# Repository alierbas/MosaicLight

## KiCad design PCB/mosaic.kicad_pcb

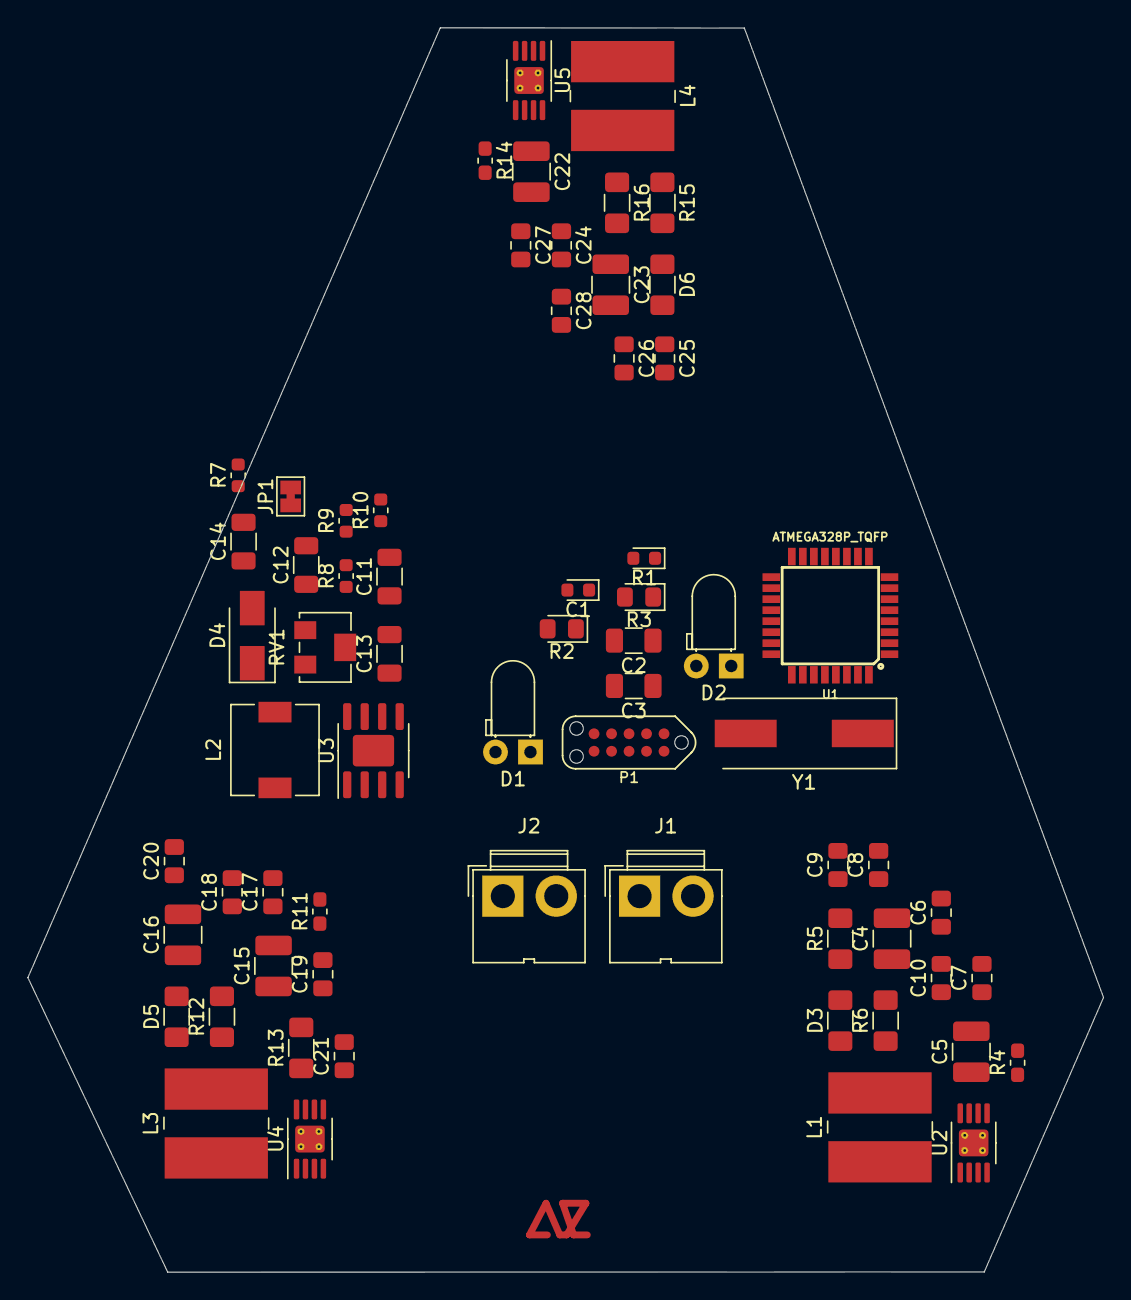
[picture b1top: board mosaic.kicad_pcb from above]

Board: 2 copper layers, 78.1 x 90.3 mm, 66 parts (0 on the bottom side), 33 nets, no tracks yet.

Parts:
C1: 0.1u; LED_0603_1608Metric
C2, C3: C; C_1206_3216Metric
C4, C5, C15, C16, C22, C23: 4.7 uF; C_1210_3225Metric_Pad1.42x2.65mm_HandSolder
C6, C17, C24: 100 nF; C_0805_2012Metric_Pad1.15x1.40mm_HandSolder
C7, C18, C25: 100nF; C_0805_2012Metric_Pad1.15x1.40mm_HandSolder
C8, C19, C26: 1.5 nF; C_0805_2012Metric_Pad1.15x1.40mm_HandSolder
C9, C20, C27: 1.5nf; C_0805_2012Metric_Pad1.15x1.40mm_HandSolder
C10, C21, C28: 1 uF; C_0805_2012Metric_Pad1.15x1.40mm_HandSolder
C11, C14: 22UF; C_1206_3216Metric
C12: 220pf; C_1206_3216Metric
C13: 100NF; C_1206_3216Metric
D1, D2: LED; LED_D3.0mm_Horizontal_O1.27mm_Z2.0mm_Clear
D3, D5, D6: B240A; C_1206_3216Metric_Pad1.42x1.75mm_HandSolder
D4: ss34; D_SMA
J1, J2: Conn_01x02_Female; JWT_A3963_1x02_P3.96mm_Vertical
JP1: SolderJumper_2_Bridged; SolderJumper-2_P1.3mm_Bridged_Pad1.0x1.5mm
L1, L3, L4: 68u H; L_Wuerth_WE-PD2-Typ-L
L2: 10UH; L_6.3x6.3_H3
P1: TC2050-IDC; TC2050-NL_SMALL
R1: 10k; LED_0603_1608Metric
R2, R3: 1k; LED_0805_2012Metric_Pad1.15x1.40mm_HandSolder
R4, R11, R14: 1k; R_0603_1608Metric_Pad1.05x0.95mm_HandSolder
R5, R12, R15: 0R1; R_1206_3216Metric_Pad1.42x1.75mm_HandSolder
R6, R13, R16: 0R2; R_1206_3216Metric_Pad1.42x1.75mm_HandSolder
R7, R8, R9: 100K; R_0603_1608Metric
R10: 6K2; R_0603_1608Metric
RV1: 50K; Potentiometer_Bourns_3224W_Vertical
U1: ATMEGA328P_TQFP; TQFP32-08
U2, U4, U5: AL8860; MSOP-8-1EP_3x3mm_P0.65mm_EP1.95x2.15mm_ThermalVias
U3: MP1584EN(SOIC8E); SOIC-8-1EP_3.9x4.9mm_P1.27mm_EP2.29x3mm
U6: Logo-c; logo - c
Y1: Crystal; Crystal_SMD_HC49-SD

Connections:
ANODE: C8.1, C10.1, C19.1, C21.1, C26.1, C28.1, R5.2, R6.2, R12.2, R13.2, R15.2, R16.2, U2.1, U4.1, U5.1
CATHODE: C9.1, C10.2, C20.1, C21.2, C27.1, C28.2, L1.2, L3.2, L4.2
DTR: C1.2, P1.6
GND: C2.2, C3.2, C4.2, C5.2, C6.2, C7.1, C8.2, C9.2, C11.2, C14.1, C15.2, C16.2, C17.2, C18.1, C19.2, C20.2, C22.2, C23.2, C24.2, C25.1, C26.2, C27.2, D1.1, D2.1, D4.2, J2.2, P1.8, R8.2, R9.2, R10.2, U1.3, U1.5, U1.21, U2.2, U2.3, U2.9, U3.5, U4.2, U4.3, U4.9, U5.2, U5.3, U5.9
MISO: P1.2, U1.16
MOSI: P1.3, U1.15
MPOWER: JP1.2, P1.10, R1.1, R2.1, U1.4, U1.6, U1.18
unnamed: C2.1, U1.7, Y1.1
unnamed: C3.1, U1.8, Y1.2
unnamed: C7.2, R4.1, U2.4
unnamed: C12.1, U3.3
unnamed: C12.2, R9.1
unnamed: C13.1, D4.1, L2.1, U3.1
unnamed: C13.2, U3.8
unnamed: C14.2, JP1.1, L2.2, RV1.3
unnamed: C18.2, R11.1, U4.4
unnamed: C25.2, R14.1, U5.4
unnamed: D1.2, R2.2
unnamed: D2.2, R3.2
unnamed: D3.2, L1.1, U2.5, U2.6
unnamed: D5.2, L3.1, U4.5, U4.6
unnamed: D6.2, L4.1, U5.5, U5.6
unnamed: R7.2, U3.2
unnamed: R8.1, U3.6
unnamed: R10.1, RV1.1, RV1.2, U3.4
PWM: R4.2, R11.2, R14.2, U1.24, U1.25, U1.26
RESET: C1.1, P1.4, R1.2, U1.29
RXI: P1.7, U1.30
SCK: P1.1, R3.1, U1.17
SCL: J1.2, U1.28
SDA: J1.1, U1.27
TXO: P1.5, U1.31
VIN: C4.1, C5.1, C6.1, C11.1, C15.1, C16.1, C17.1, C22.1, C23.1, C24.1, D3.1, D5.1, D6.1, J2.1, R5.1, R6.1, R7.1, R12.1, R13.1, R15.1, R16.1, U2.8, U3.7, U4.8, U5.8

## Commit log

2020-04-17 first init
2020-04-17 init second
